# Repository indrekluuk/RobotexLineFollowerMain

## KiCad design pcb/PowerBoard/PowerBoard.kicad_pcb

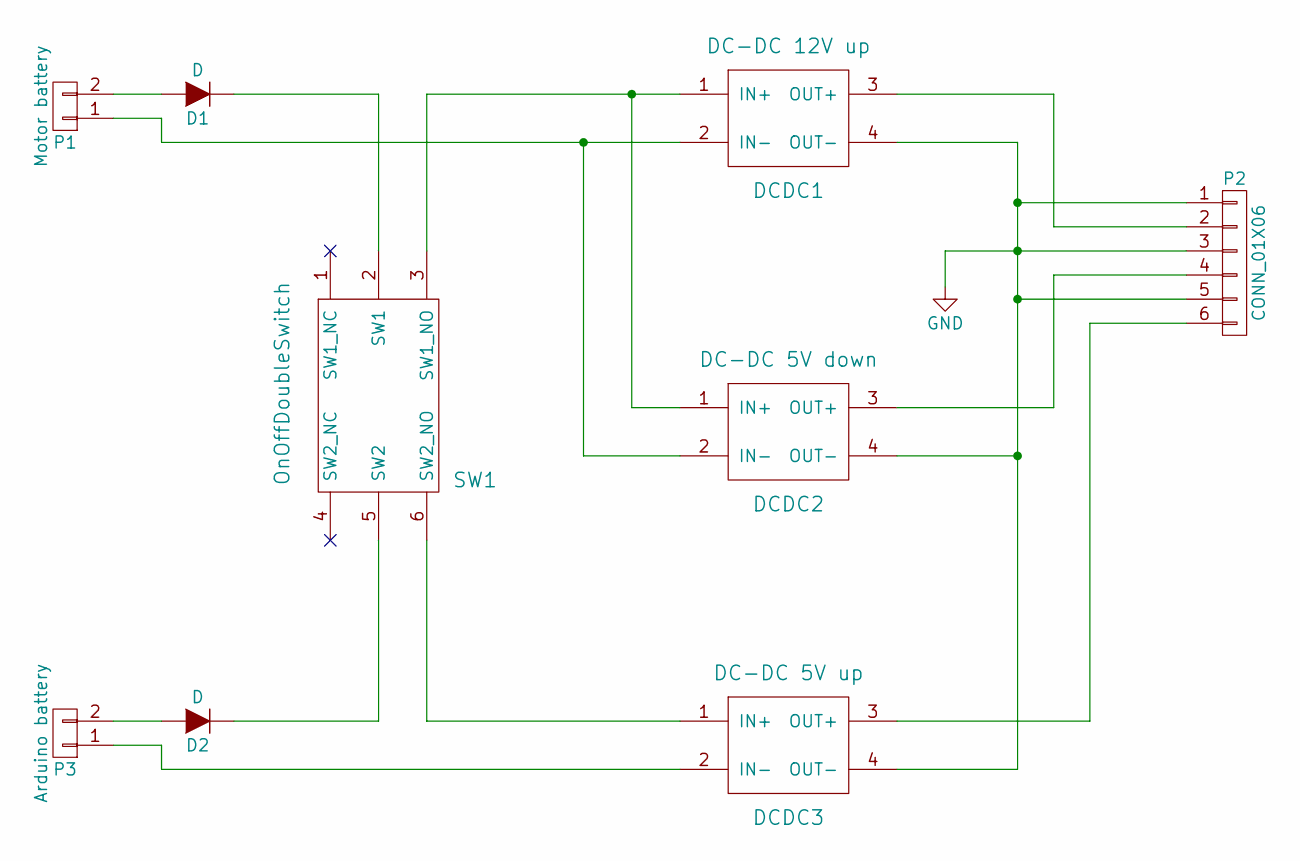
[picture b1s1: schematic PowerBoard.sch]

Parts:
D1, D2: D; Diode_DO-35_SOD27_Horizontal_RM10
DCDC1: DC-DC 12V up; DcDcAdjustableUp
DCDC2: DC-DC 5V down; DcDcAdjustableDown
DCDC3: DC-DC 5V up; DcDc5VUp
P1: Motor battery; Pin_Header_Straight_1x02
P2: CONN_01X06; Pin_Header_Straight_1x06
P3: Arduino battery; Pin_Header_Straight_1x02
SW1: OnOffDoubleSwitch

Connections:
GND: DCDC1.4 (OUT-), DCDC2.4 (OUT-), DCDC3.4 (OUT-), P2.1, P2.3, P2.5
unnamed: D1.1 (K), SW1.2 (SW1)
unnamed: D1.2 (A), P1.2
unnamed: D2.1 (K), SW1.5 (SW2)
unnamed: D2.2 (A), P3.2
unnamed: DCDC1.1 (IN+), DCDC2.1 (IN+), SW1.3 (SW1_NO)
unnamed: DCDC1.2 (IN-), DCDC2.2 (IN-), P1.1
unnamed: DCDC1.3 (OUT+), P2.2
unnamed: DCDC2.3 (OUT+), P2.4
unnamed: DCDC3.1 (IN+), SW1.6 (SW2_NO)
unnamed: DCDC3.2 (IN-), P3.1
unnamed: DCDC3.3 (OUT+), P2.6

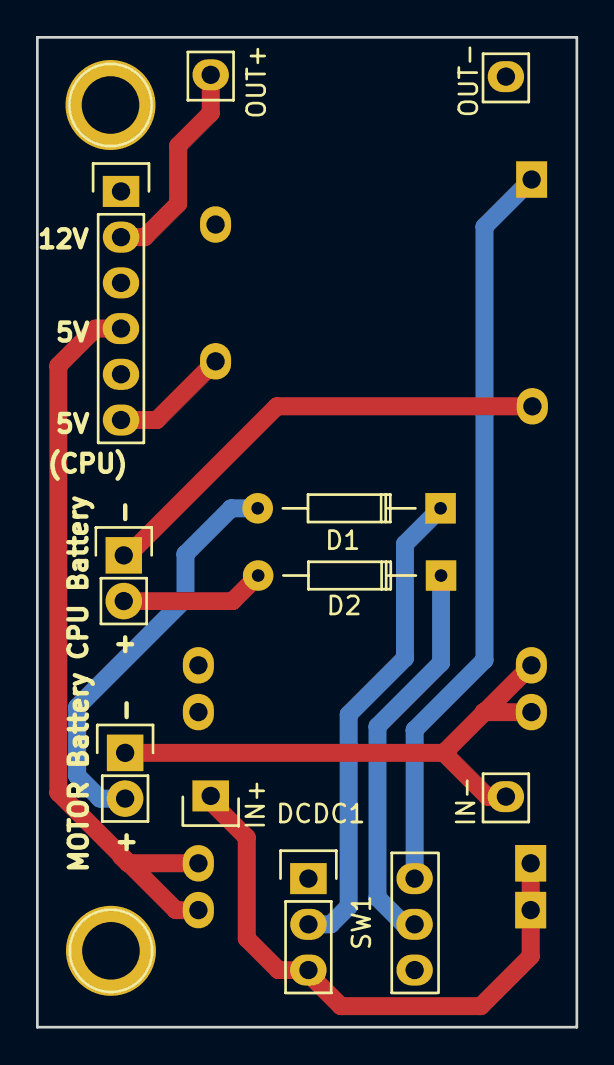
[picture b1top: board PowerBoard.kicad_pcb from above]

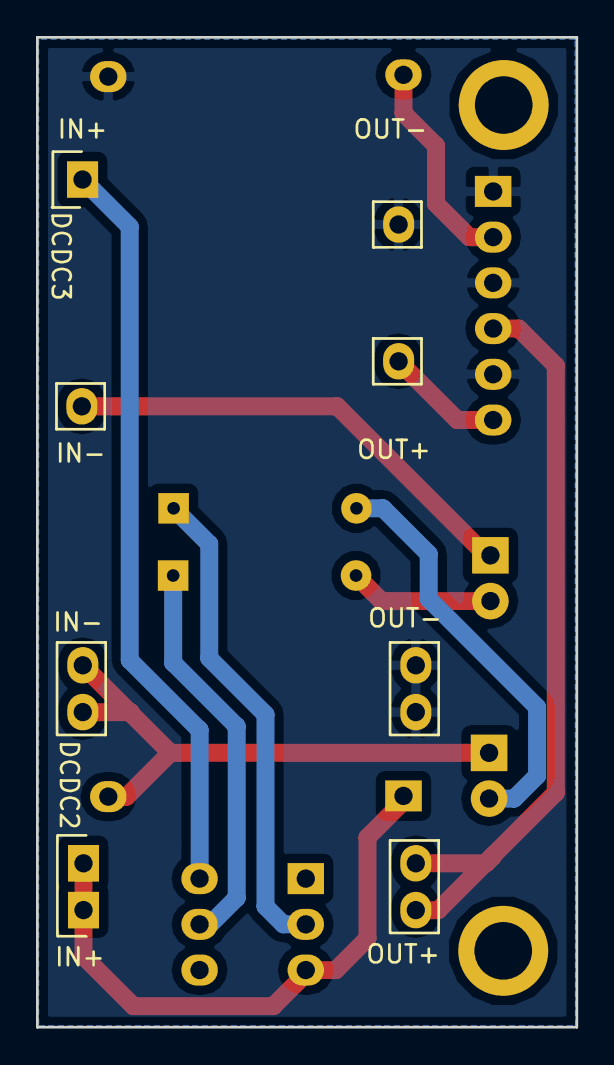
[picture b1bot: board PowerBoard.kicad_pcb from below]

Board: 2 copper layers, 30.0 x 55.0 mm, 9 parts (2 on the bottom side), 12 nets.

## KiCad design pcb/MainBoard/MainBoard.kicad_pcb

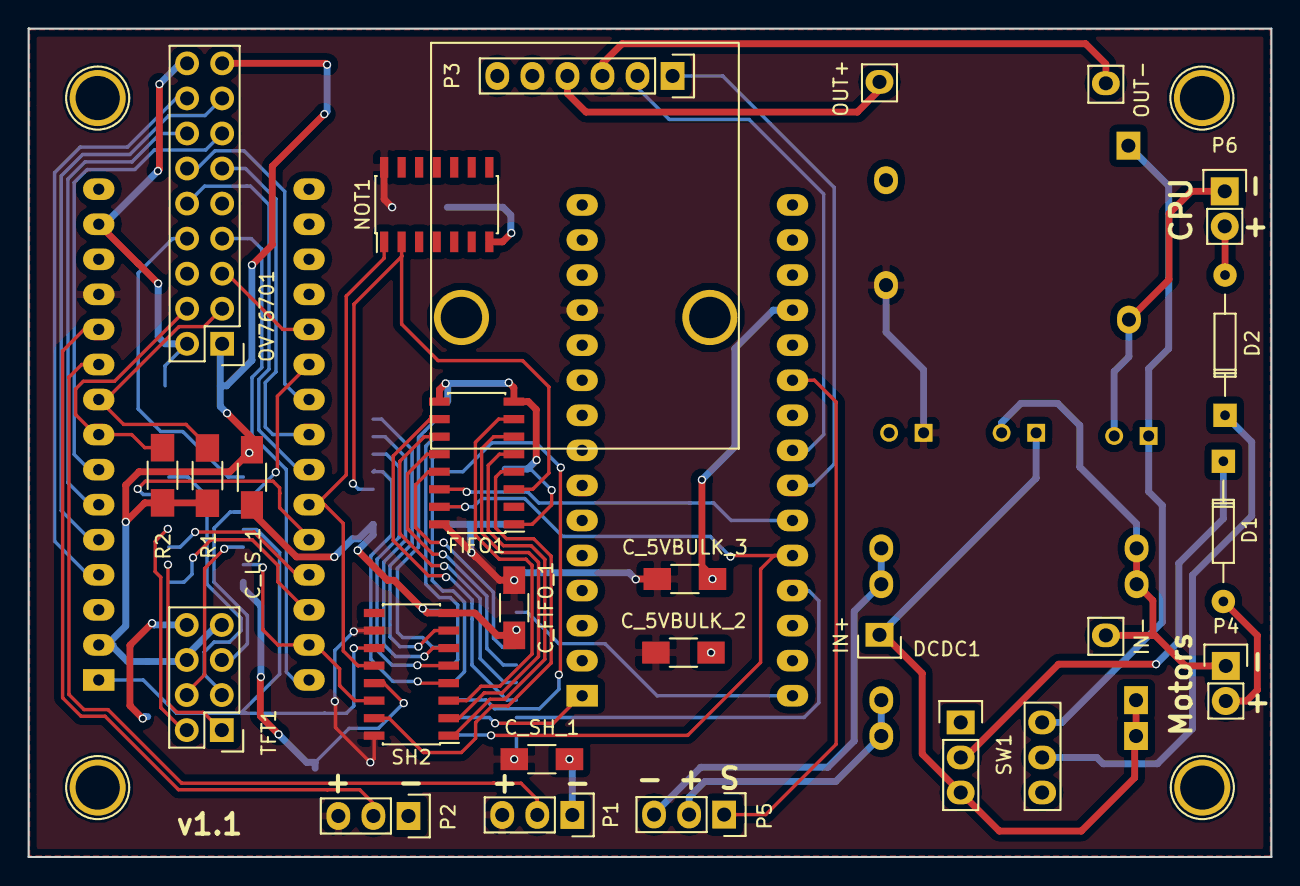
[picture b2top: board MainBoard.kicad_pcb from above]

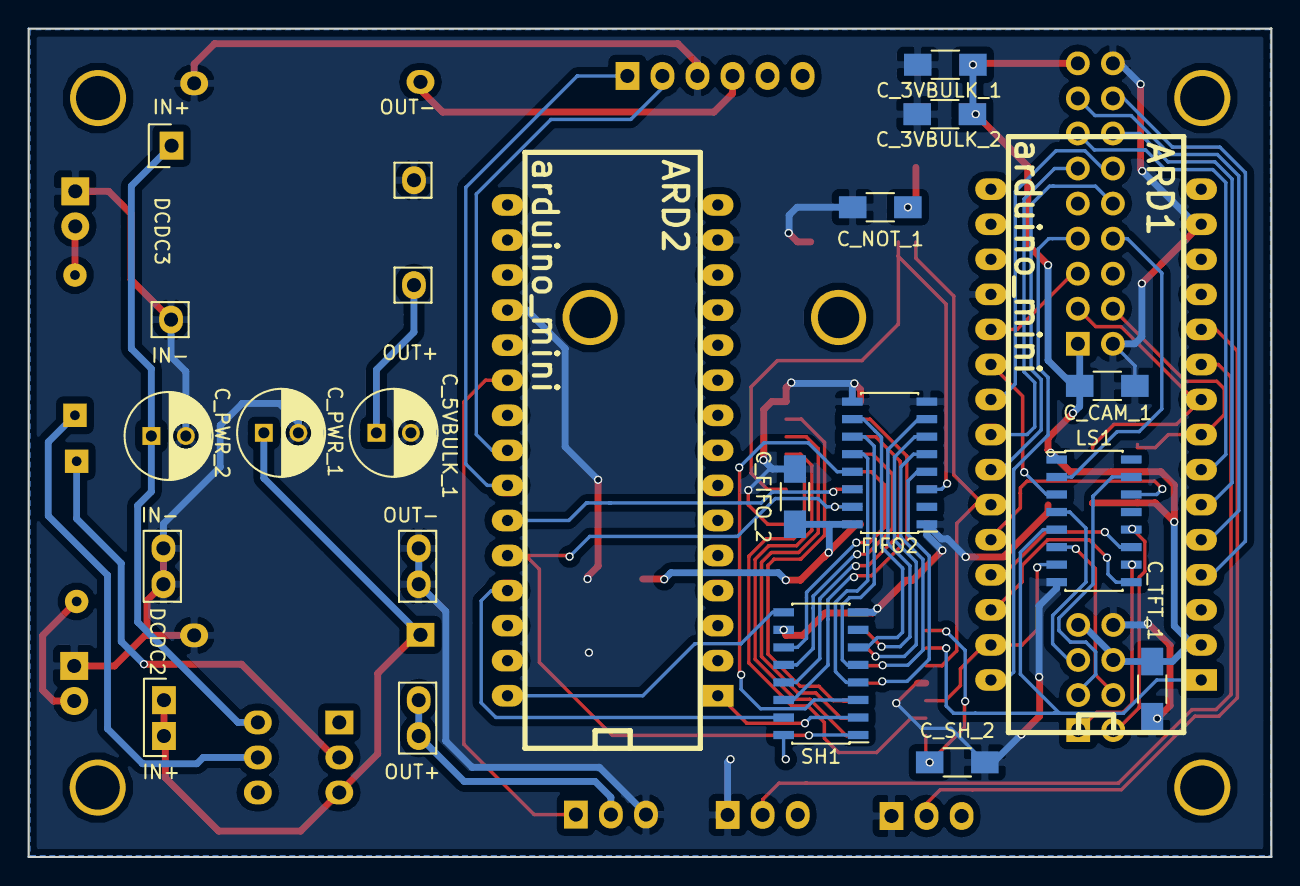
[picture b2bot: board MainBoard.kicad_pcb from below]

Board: 2 copper layers, 90.0 x 60.0 mm, 39 parts (17 on the bottom side), 62 nets.

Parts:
ARD1, ARD2: arduino_mini
C_3VBULK_1, C_3VBULK_2, C_5VBULK_2, C_5VBULK_3: 10-100uF; C_1206_HandSoldering
C_5VBULK_1: 10-100uF; C_Radial_D6.3_L11.2_P2.5
C_CAM_1: 1uF; C_1206_HandSoldering
C_FIFO_1, C_FIFO_2: 0.1uF; C_1206_HandSoldering
C_LS_1: 0.1uF; C_1206_HandSoldering
C_NOT_1: 0.1uF; C_1206_HandSoldering
C_PWR_1, C_PWR_2: C; C_Radial_D6.3_L11.2_P2.5
C_SH_1, C_SH_2: 0.1uF; C_1206_HandSoldering
C_TFT_1: 1uF; C_1206_HandSoldering
D1, D2: D_Schottky; Diode_DO-35_SOD27_Horizontal_RM10
DCDC1: DC-DC 12V up; DcDcAdjustableUp
DCDC2: DC-DC 5V down; DcDcAdjustableDown
DCDC3: DC-DC 5V up; DcDc5VUp
FIFO1, FIFO2: fifo_74HC40105; SOIC-16_3.9x9.9mm_Pitch1.27mm
LS1: LevelShifter_74HC4050D; SOIC-16_3.9x9.9mm_Pitch1.27mm
NOT1: notgate_74HCT04; SOIC-14_3.9x8.7mm_Pitch1.27mm
OV76701: Camera_OV7670; Pin_Header_Straight_2x09
P1: Camera pot 1; Pin_Header_Straight_1x03
P2: Camera pot 2; Pin_Header_Straight_1x03
P3: Motor controller; MotorController
P4: Motor battery; Pin_Header_Straight_1x02
P5: Steering connector; Pin_Header_Straight_1x03
P6: Arduino battery; Pin_Header_Straight_1x02
R1, R2: 10k; R_1206_HandSoldering
SH1: shiftregister_74HC165; SOIC-16_3.9x9.9mm_Pitch1.27mm
SH2: shiftregister_74HC595; SOIC-16_3.9x9.9mm_Pitch1.27mm
SW1: OnOffDoubleSwitch
TFT1: TFT_1.8inch; Pin_Header_Straight_2x04

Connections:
+5V: ARD1.12, ARD2.12, C_5VBULK_1.1, C_5VBULK_2.1, C_5VBULK_3.1, C_FIFO_1.1, C_FIFO_2.1, C_NOT_1.1, C_SH_1.1, C_SH_2.1, DCDC3.3, FIFO1.16, FIFO2.16, NOT1.14, P1.3, P2.3, SH1.16, SH2.10, SH2.16
/SectionCommBuffer/DATA_READY: ARD2.25, FIFO1.14
/SectionCommBuffer/FIFO_POP: ARD2.26, FIFO1.15, FIFO2.15, SH1.1
/SectionCommBuffer/FIFO_PUSH: ARD1.25, NOT1.1, SH2.12
/SectionMainControl/FIFO_ENABLE: ARD2.27, SH1.15
/SectionMainControl/FORWARD: ARD2.24, P3.1
/SectionMainControl/SPI_CLOCK: ARD2.1, SH1.2
/SectionMainControl/SPI_DATA_IN: ARD2.30, SH1.9
/SectionMainControl/STEERING: ARD2.21, P5.1
/SectionPower/MOTOR_A2: ARD2.23, P3.2
/Sheet57F22415/Pixel_D0: ARD1.4, OV76701.16
/Sheet57F22415/Pixel_D1: ARD1.5, OV76701.15
/Sheet57F22415/Pixel_D2: ARD1.6, OV76701.14
/Sheet57F22415/Pixel_D3: ARD1.7, OV76701.13
/Sheet57F22415/Pixel_D4: ARD1.22, OV76701.12
/Sheet57F22415/Pixel_D5: ARD1.23, OV76701.11
/Sheet57F22415/Pixel_D6: ARD1.24, OV76701.10
/Sheet57F22415/SPI_CLOCK: ARD1.1, LS1.5, SH2.11
/Sheet57F22415/SPI_DATA: ARD1.29, LS1.7, SH2.14
GND: ARD1.14, ARD1.19, ARD2.14, ARD2.19, C_3VBULK_1.2, C_3VBULK_2.2, C_5VBULK_1.2, C_5VBULK_2.2, C_5VBULK_3.2, C_CAM_1.2, C_FIFO_1.2, C_FIFO_2.2, C_LS_1.2, C_NOT_1.2, C_PWR_1.2, C_PWR_2.2, C_SH_1.2, C_SH_2.2, C_TFT_1.2, DCDC1.2, DCDC1.4, DCDC2.2, DCDC2.4, DCDC3.2, DCDC3.4, FIFO1.1, FIFO1.8, FIFO1.9, FIFO2.1, FIFO2.8, FIFO2.9, LS1.8, NOT1.7, OV76701.2, OV76701.18, P1.1, P2.1, P3.3, P4.1, P5.3, P6.1, SH1.8, SH1.10, SH2.8, SH2.13, TFT1.8
unnamed: ARD1.2, C_3VBULK_1.1, C_3VBULK_2.1, C_CAM_1.1, C_LS_1.1, C_TFT_1.1, LS1.1, OV76701.1, OV76701.17, R1.1, R2.1, TFT1.6, TFT1.7
unnamed: ARD1.8, OV76701.4, R2.2
unnamed: ARD1.9, OV76701.3, R1.2
unnamed: ARD1.10, P1.2
unnamed: ARD1.11, P2.2
unnamed: ARD1.20, OV76701.5
unnamed: ARD1.21, LS1.3
unnamed: ARD1.26, LS1.14
unnamed: ARD1.27, LS1.11
unnamed: ARD1.28, LS1.9
unnamed: ARD1.30, OV76701.7
unnamed: C_PWR_1.1, DCDC1.1, DCDC2.1, SW1.3
unnamed: C_PWR_2.1, DCDC3.1, SW1.6
unnamed: D1.1, SW1.2
unnamed: D1.2, P4.2
unnamed: D2.1, SW1.5
unnamed: D2.2, P6.2
unnamed: DCDC1.3, P3.4
unnamed: DCDC2.3, P5.2
unnamed: FIFO1.3, FIFO2.3, NOT1.2
unnamed: FIFO1.4, SH2.15
unnamed: FIFO1.5, SH2.1
unnamed: FIFO1.6, SH2.2
unnamed: FIFO1.7, SH2.3
unnamed: FIFO1.10, SH1.14
unnamed: FIFO1.11, SH1.13
unnamed: FIFO1.12, SH1.12
unnamed: FIFO1.13, SH1.11
unnamed: FIFO2.4, SH2.4
unnamed: FIFO2.5, SH2.5
unnamed: FIFO2.6, SH2.6
unnamed: FIFO2.7, SH2.7
unnamed: FIFO2.10, SH1.6
unnamed: FIFO2.11, SH1.5
unnamed: FIFO2.12, SH1.4
unnamed: FIFO2.13, SH1.3
unnamed: LS1.2, OV76701.8
unnamed: LS1.4, TFT1.5
unnamed: LS1.6, TFT1.4
unnamed: LS1.10, TFT1.1
unnamed: LS1.12, TFT1.2
unnamed: LS1.15, TFT1.3

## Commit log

2016-07-10 power board layout done
2016-07-11 power board ready
2016-10-02 byte receiving is now working
2016-10-02 buffered read
2016-10-02 static delay is faster
2016-10-03 ignore file for doc folder
2016-10-09 schema for unified board
2016-10-09 removed unnecessary files
2016-10-09 PCB design finished
2016-10-09 generated gerber files
2016-10-30 restructured project files
2016-10-30 example tests are now running properly
2016-11-05 fixed power module ground connections
2016-11-05 re-assigned data ready from pin 10 to pin 7.
2016-11-08 working solution
2016-11-12 new line transfer data format
2016-11-13 separate class for line position finder
2016-11-13 test for line class
2016-11-13 detect turn
2016-11-13 print out detected line end
2016-11-13 test turn other way
2016-11-13 additional tests
2016-11-13 no interrupts during data read
2016-11-26 clean-up
2016-11-27 new structure
2016-11-27 steer frown wheels
2016-11-27 steering with range limit
2016-11-27 steer
2016-11-27 init front wheels separately for better debugging
2016-11-27 separate class for steering mapping
2016-11-27 drive forward
2016-11-27 working with simple track
2016-11-28 working solution 2
2016-11-28 LineSegment more generic
2016-11-28 Map screen to world coordinates
2016-11-28 track world X
2016-11-28 restored use directly screen coordinates
2016-11-28 if line is lost then turn to last seen line direction
2016-11-29 detect lost line by starting point of the line
2016-11-29 use bitfield structure for message
2016-11-29 end of line and egnine reverse
2016-11-29 check for sharp turn
2016-11-29 reversing
2016-11-30 removed sharp turn detection. Too flaky
2016-11-30 wiggle wheels if stuck
2016-12-01 line index to screen to world map
2016-12-02 give boost if doesn't move for 3 seconds
